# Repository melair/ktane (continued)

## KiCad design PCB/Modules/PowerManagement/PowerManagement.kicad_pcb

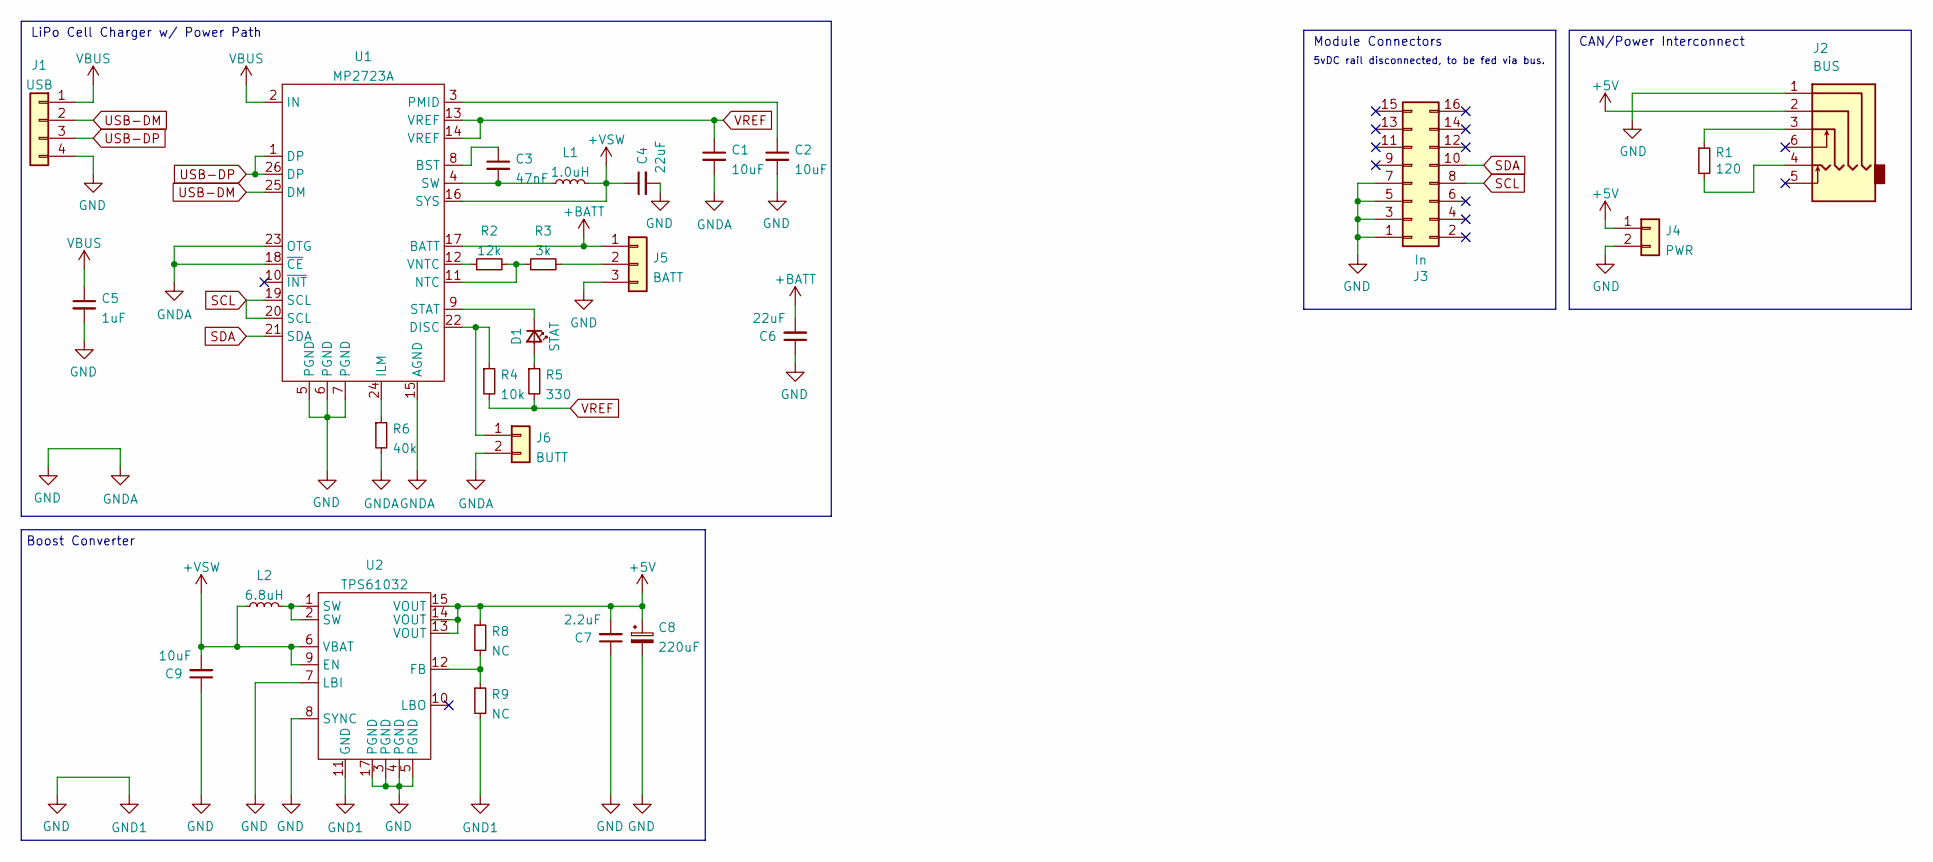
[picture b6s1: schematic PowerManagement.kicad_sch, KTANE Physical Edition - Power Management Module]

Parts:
C1, C9: 10uF; C_0805_2012Metric
C2: 10uF; C_1206_3216Metric
C3: 47nF; C_0603_1608Metric
C4, C6: 22uF; C_0805_2012Metric
C5: 1uF; C_0603_1608Metric
C7: 2.2uF; C_0603_1608Metric
C8: 220uF; CP_EIA-7343-20_Kemet-V
D1: STAT; LED_0805_2012Metric
J1: USB; PinHeader_1x04_P2.54mm_Vertical
J2: BUS; Jack_3.5mm_PJ311_Horizontal
J3: In; PinHeader_2x08_P2.54mm_Vertical-Centered
J4: PWR; JST_XH_B2B-XH-A_1x02_P2.50mm_Vertical
J5: BATT; JST_PH_B3B-PH-K_1x03_P2.00mm_Vertical
J6: BUTT; JST_PH_B2B-PH-K_1x02_P2.00mm_Vertical
L1: 1.0uH; PA5001
L2: 6.8uH; DR124
R1: 120; R_0805_2012Metric
R2: 12k; R_0805_2012Metric
R3: 3k; R_0805_2012Metric
R4: 10k; R_0805_2012Metric
R5: 330; R_0805_2012Metric
R6: 40k; R_0805_2012Metric
R8, R9: NC; R_0805_2012Metric
U1: MP2723A; MP2723AGQC-0000-P
U2: TPS61032; TSSOP-16-1EP_4.4x5mm_P0.65mm

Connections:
+5V: C7.2, C8.1, J2.2, J4.1, R8.1, U2.13 (VOUT), U2.14 (VOUT), U2.15 (VOUT)
+BATT: C6.2, J5.1, U1.17 (BATT)
+VSW: C4.1, C9.2, L1.2, L2.1, U1.16 (SYS), U2.6 (VBAT), U2.9 (EN)
GND: C1.2, C2.2, C4.2, C5.2, C6.1, C7.1, C8.2, C9.1, J1.4, J2.1, J3.1, J3.3, J3.5, J3.7, J4.2, J5.3, J6.2, R6.2, R9.2, U1.5 (PGND), U1.6 (PGND), U1.7 (PGND), U1.15 (AGND), U1.18 (~CE), U1.23 (OTG), U2.3 (PGND), U2.4 (PGND), U2.5 (PGND), U2.7 (LBI), U2.8 (SYNC), U2.11 (GND), U2.17 (PGND)
unnamed: C2.1, U1.3 (PMID)
unnamed: C3.1, U1.8 (BST)
unnamed: C3.2, L1.1, U1.4 (SW)
unnamed: D1.1 (K), U1.9 (STAT)
unnamed: D1.2 (A), R5.1
unnamed: J2.3, R1.1
unnamed: J2.4, R1.2
unnamed: J5.2, R3.2
unnamed: J6.1, R4.1, U1.22 (DISC)
unnamed: L2.2, U2.1 (SW), U2.2 (SW)
unnamed: R2.1, U1.12 (VNTC)
unnamed: R2.2, R3.1, U1.11 (NTC)
unnamed: R6.1, U1.24 (ILM)
unnamed: R8.2, R9.1, U2.12 (FB)
SCL: J3.8, U1.19 (SCL), U1.20 (SCL)
SDA: J3.10, U1.21 (SDA)
USB-DM: J1.2, U1.25 (DM)
USB-DP: J1.3, U1.1 (DP), U1.26 (DP)
VBUS: C5.1, J1.1, U1.2 (IN)
VREF: C1.1, R4.2, R5.2, U1.13 (VREF), U1.14 (VREF)

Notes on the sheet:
Boost Converter
Module Connectors
5vDC rail disconnected, to be fed via bus.
LiPo Cell Charger w/ Power Path
CAN/Power Interconnect

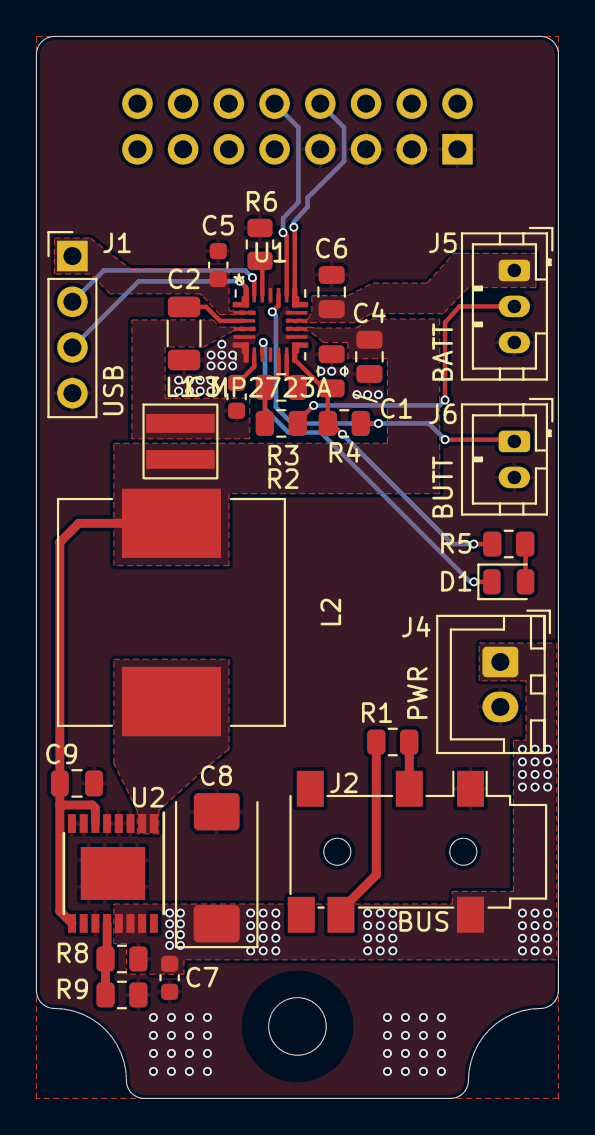
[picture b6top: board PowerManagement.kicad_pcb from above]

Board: 2 copper layers, 29.0 x 59.0 mm, 28 parts (1 on the bottom side), 24 nets.

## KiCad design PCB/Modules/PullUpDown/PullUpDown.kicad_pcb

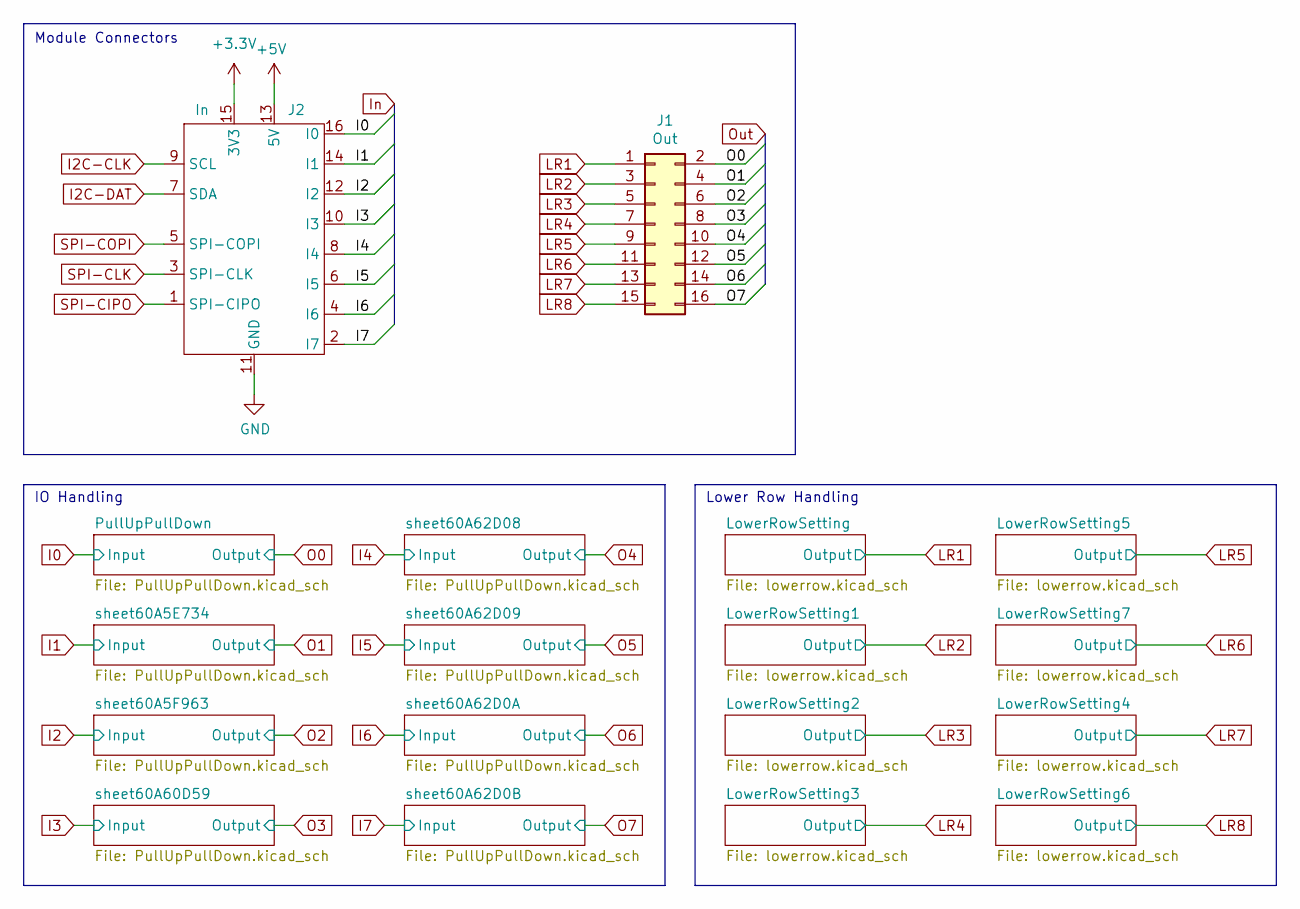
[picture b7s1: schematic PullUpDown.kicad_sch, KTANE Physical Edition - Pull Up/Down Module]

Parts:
J1: Out; PinHeader_2x08_P2.54mm_Vertical-Centered; DIGIKEY S9171-ND
J2: In; KTANE Submodule Connector V2 - Short; DIGIKEY STOCK

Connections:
+3.3V: J2.15 (3V3); also elsewhere on the board
+5V: J2.13 (5V); also elsewhere on the board
GND: J2.11 (GND); also elsewhere on the board
I0: J2.16 (I0); also elsewhere on the board
I1: J2.14 (I1); also elsewhere on the board
I2: J2.12 (I2); also elsewhere on the board
I2C-CLK: J2.9 (SCL)
I2C-DAT: J2.7 (SDA)
I3: J2.10 (I3); also elsewhere on the board
I4: J2.8 (I4); also elsewhere on the board
I5: J2.6 (I5); also elsewhere on the board
I6: J2.4 (I6); also elsewhere on the board
I7: J2.2 (I7); also elsewhere on the board
LR1: J1.1; also elsewhere on the board
LR2: J1.3; also elsewhere on the board
LR3: J1.5; also elsewhere on the board
LR4: J1.7; also elsewhere on the board
LR5: J1.9; also elsewhere on the board
LR6: J1.11; also elsewhere on the board
LR7: J1.13; also elsewhere on the board
LR8: J1.15; also elsewhere on the board
O0: J1.2; also elsewhere on the board
O1: J1.4; also elsewhere on the board
O2: J1.6; also elsewhere on the board
O3: J1.8; also elsewhere on the board
O4: J1.10; also elsewhere on the board
O5: J1.12; also elsewhere on the board
O6: J1.14; also elsewhere on the board
O7: J1.16; also elsewhere on the board
SPI-CIPO: J2.1 (SPI-CIPO)
SPI-CLK: J2.3 (SPI-CLK)
SPI-COPI: J2.5 (SPI-COPI)

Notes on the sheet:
Module Connectors
IO Handling
Lower Row Handling

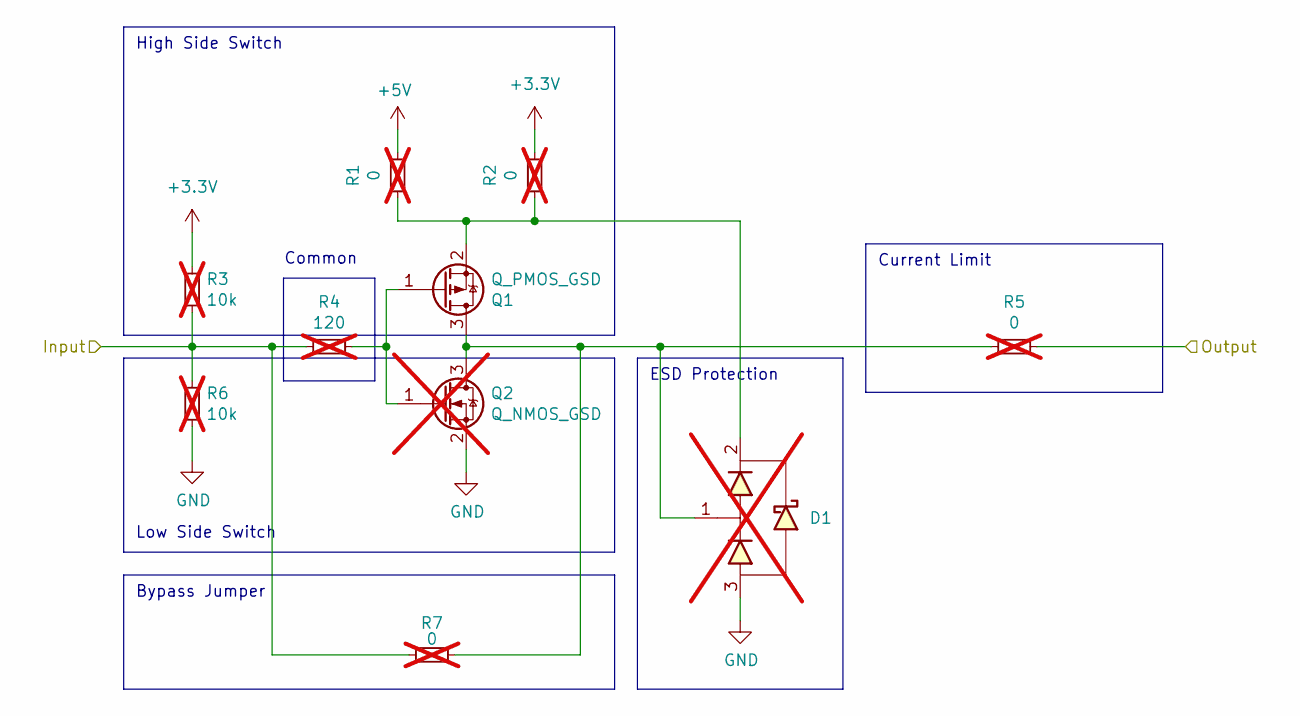
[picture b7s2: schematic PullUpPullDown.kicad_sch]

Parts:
D1: D1213A-01SO-7; SOT-23; DIGIKEY D1213A-01SO-7DICT-ND; not fitted
Q1: Q_PMOS_GSD; SOT-23; DIGIKEY DMG2301L-7DICT-ND
Q2: Q_NMOS_GSD; SOT-23; DIGIKEY 31-DMN2310U-7CT-ND; not fitted
R1, R2, R5, R7: 0; R_0603_1608Metric; DIGIKEY 10-ERJ-H3G0R00VCT-ND; not fitted
R3, R6: 10k; R_0603_1608Metric; DIGIKEY P10.0KHCT-ND; not fitted
R4: 120; R_0603_1608Metric; DIGIKEY P120HCT-ND; not fitted

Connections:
+3.3V: R2.1, R3.2; also elsewhere on the board
+5V: R1.1; also elsewhere on the board
GND: D1.3, Q2.2 (S), R6.1; also elsewhere on the board
I0: R3.1, R4.1, R6.2, R7.2; also elsewhere on the board
unnamed: D1.1, Q1.3 (D), Q2.3 (D), R5.2, R7.1
unnamed: Q1.1 (G), Q2.1 (G), R4.2
unnamed: D1.2, Q1.2 (S), R1.2, R2.2
O0: R5.1; also elsewhere on the board

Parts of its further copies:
D2, D3, D4, D5, D6, D7, D8: D1213A-01SO-7; SOT-23; DIGIKEY D1213A-01SO-7DICT-ND; not fitted
Q3, Q5, Q7, Q9, Q11, Q13, Q15: Q_PMOS_GSD; SOT-23; DIGIKEY DMG2301L-7DICT-ND
Q4, Q6, Q8, Q10, Q12, Q14, Q16: Q_NMOS_GSD; SOT-23; DIGIKEY 31-DMN2310U-7CT-ND; not fitted
R8, R9, R12, R14, R15, R16, R19, R21, R22, R23, R26, R28, R29, R30, R33, R35, R36, R37, R40, R42, R43, R44, R47, R49, R50, R51, R54, R56: 0; R_0603_1608Metric; DIGIKEY 10-ERJ-H3G0R00VCT-ND; not fitted
R10, R13, R17, R20, R24, R27, R31, R34, R38, R41, R45, R48, R52, R55: 10k; R_0603_1608Metric; DIGIKEY P10.0KHCT-ND; not fitted

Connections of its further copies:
+3.3V: R9.1, R10.2, R16.1, R17.2, R23.1, R24.2, R30.1, R31.2, R37.1, R38.2, R44.1, R45.2, R51.1, R52.2; also elsewhere on the board
+5V: R8.1, R15.1, R22.1, R29.1, R36.1, R43.1, R50.1; also elsewhere on the board
GND: D2.3, D3.3, D4.3, D5.3, D6.3, D7.3, D8.3, Q4.2 (S), Q6.2 (S), Q8.2 (S), Q10.2 (S), Q12.2 (S), Q14.2 (S), Q16.2 (S), R13.1, R20.1, R27.1, R34.1, R41.1, R48.1, R55.1; also elsewhere on the board
I1: R10.1, R13.2, R14.2; also elsewhere on the board
I2: R17.1, R20.2, R21.2; also elsewhere on the board
I3: R24.1, R27.2, R28.2; also elsewhere on the board
I4: R31.1, R34.2, R35.2; also elsewhere on the board
I5: R38.1, R41.2, R42.2; also elsewhere on the board
I6: R45.1, R48.2, R49.2; also elsewhere on the board
I7: R52.1, R55.2, R56.2; also elsewhere on the board
unnamed: D2.1, Q3.3 (D), Q4.3 (D), R12.2, R14.1
unnamed 25: Q3.1 (G), Q4.1 (G); also elsewhere on the board
unnamed: D2.2, Q3.2 (S), R8.2, R9.2
unnamed: D3.1, Q5.3 (D), Q6.3 (D), R19.2, R21.1
unnamed 28: Q5.1 (G), Q6.1 (G); also elsewhere on the board
unnamed: D3.2, Q5.2 (S), R15.2, R16.2
unnamed: D4.1, Q7.3 (D), Q8.3 (D), R26.2, R28.1
unnamed 31: Q7.1 (G), Q8.1 (G); also elsewhere on the board
unnamed: D4.2, Q7.2 (S), R22.2, R23.2
unnamed: D5.2, Q9.2 (S), R29.2, R30.2
unnamed: D5.1, Q9.3 (D), Q10.3 (D), R33.2, R35.1
unnamed 35: Q9.1 (G), Q10.1 (G); also elsewhere on the board
unnamed: D6.1, Q11.3 (D), Q12.3 (D), R40.2, R42.1
unnamed 37: Q11.1 (G), Q12.1 (G); also elsewhere on the board
unnamed: D6.2, Q11.2 (S), R36.2, R37.2
unnamed: D7.1, Q13.3 (D), Q14.3 (D), R47.2, R49.1
unnamed 40: Q13.1 (G), Q14.1 (G); also elsewhere on the board
unnamed: D7.2, Q13.2 (S), R43.2, R44.2
unnamed: D8.1, Q15.3 (D), Q16.3 (D), R54.2, R56.1
unnamed 43: Q15.1 (G), Q16.1 (G); also elsewhere on the board
unnamed: D8.2, Q15.2 (S), R50.2, R51.2
O1: R12.1; also elsewhere on the board
O2: R19.1; also elsewhere on the board
O3: R26.1; also elsewhere on the board
O4: R33.1; also elsewhere on the board
O5: R40.1; also elsewhere on the board
O6: R47.1; also elsewhere on the board
O7: R54.1; also elsewhere on the board

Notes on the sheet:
ESD Protection
High Side Switch
Common
Current Limit
Bypass Jumper
Low Side Switch

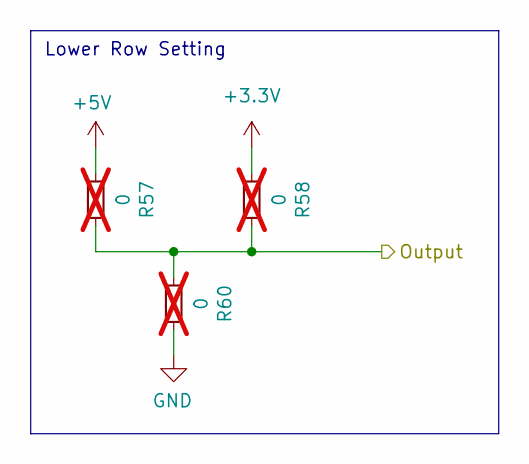
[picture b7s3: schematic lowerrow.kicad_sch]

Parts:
R57, R58, R60: 0; R_0603_1608Metric; DIGIKEY 10-ERJ-H3G0R00VCT-ND; not fitted

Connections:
+3.3V: R58.2; also elsewhere on the board
+5V: R57.2; also elsewhere on the board
GND: R60.1; also elsewhere on the board
LR1: R57.1, R58.1, R60.2; also elsewhere on the board

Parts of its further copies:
R61, R62, R64, R65, R66, R68, R69, R70, R72, R73, R74, R76, R77, R78, R80, R81, R82, R84, R85, R86, R88: 0; R_0603_1608Metric; DIGIKEY 10-ERJ-H3G0R00VCT-ND; not fitted

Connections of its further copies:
+3.3V: R62.2, R66.2, R70.2, R74.2, R78.2, R82.2, R86.2; also elsewhere on the board
+5V: R61.2, R65.2, R69.2, R73.2, R77.2, R81.2, R85.2; also elsewhere on the board
GND: R64.1, R68.1, R72.1, R76.1, R80.1, R84.1, R88.1; also elsewhere on the board
LR2: R61.1, R62.1, R64.2; also elsewhere on the board
LR3: R65.1, R66.1, R68.2; also elsewhere on the board
LR4: R69.1, R70.1, R72.2; also elsewhere on the board
LR5: R73.1, R74.1, R76.2; also elsewhere on the board
LR6: R77.1, R78.1, R80.2; also elsewhere on the board
LR7: R81.1, R82.1, R84.2; also elsewhere on the board
LR8: R85.1, R86.1, R88.2; also elsewhere on the board

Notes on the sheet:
Lower Row Setting

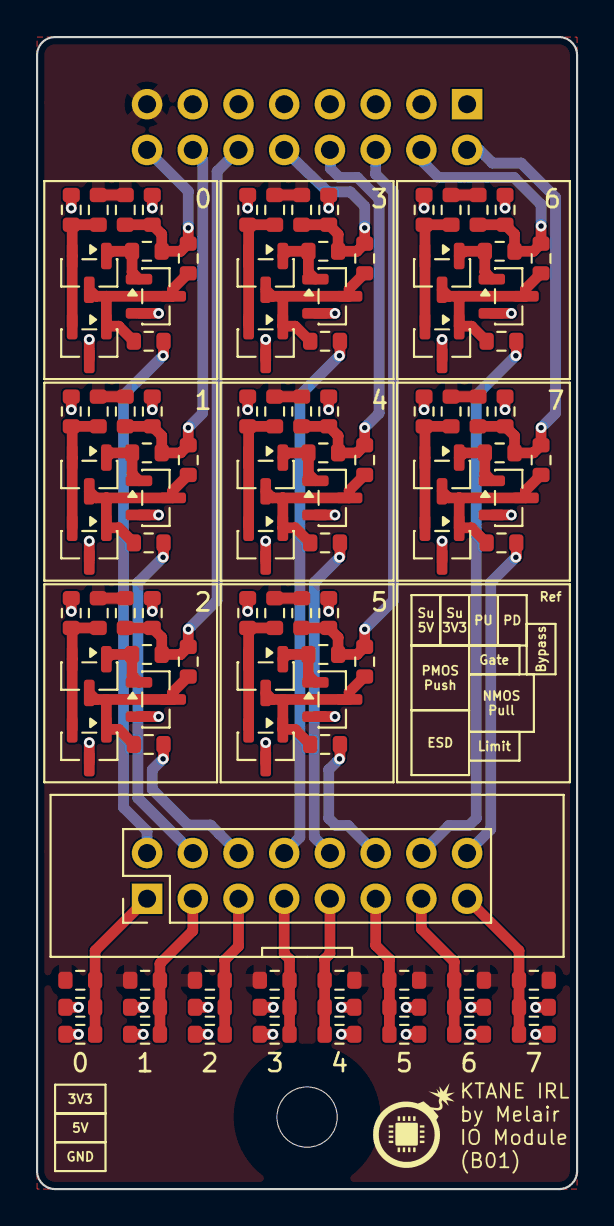
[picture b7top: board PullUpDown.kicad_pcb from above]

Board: 4 copper layers, 30.0 x 64.0 mm, 106 parts (0 on the bottom side), 51 nets.

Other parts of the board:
R11, R18, R25, R32, R39, R46, R53: 100; R_0603_1608Metric

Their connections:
I1: R11.1; also elsewhere on the board
I2: R18.1; also elsewhere on the board
I3: R25.1; also elsewhere on the board
I4: R32.1; also elsewhere on the board
I5: R39.1; also elsewhere on the board
I6: R46.1; also elsewhere on the board
I7: R53.1; also elsewhere on the board
unnamed 25: R11.2; also elsewhere on the board
unnamed 28: R18.2; also elsewhere on the board
unnamed 31: R25.2; also elsewhere on the board
unnamed 35: R32.2; also elsewhere on the board
unnamed 37: R39.2; also elsewhere on the board
unnamed 40: R46.2; also elsewhere on the board
unnamed 43: R53.2; also elsewhere on the board
